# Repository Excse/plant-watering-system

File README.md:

# 🌱 Smart Plant Pot

An ESP32-based plant pot project combining soil moisture sensing, Home Assistant integration, a custom PCB, and a planned automatic watering system with an internal reservoir.

[Getting started](#getting-started) · [Firmware guide](firmware/README.md) · [Hardware guide](docs/README.md) · [Development checklist](#development-checklist) · [PCB previews](#pcb-previews)

> **Work in progress:** firmware and electronics are being prototyped. Soil moisture readings and MQTT discovery are implemented; the complete automatic watering pot is still under development.

## Current status

| Area | Available today | Still planned |
| --- | --- | --- |
| Firmware | GPIO 34 moisture readings, calibration, Wi-Fi, MQTT state and Home Assistant discovery | Pump control, reservoir sensing, automatic watering and manual watering commands |
| Electronics | Editable KiCad schematic, board layout and generated previews | Prototype assembly and validation |
| Pot | Integrated reservoir and electronics concept | Printable design, assembly instructions and plant trials |

The repository currently supports testing moisture sensing on an ESP32 development
board. Pot CAD files and a complete assembly guide are not included yet.

## The plant pot

The pot is intended to take care of routine watering while keeping everything in one unit:

- A soil moisture sensor measures when the plant needs water.
- A pump delivers water from an internal reservoir.
- A water level sensor monitors the reservoir so the system knows when it needs refilling.
- Custom firmware manages sensing, watering, and communication with Home Assistant over Wi-Fi and MQTT.
- A custom PCB and printable pot bring the electronics and water system together, with access for refilling and maintenance.

Home Assistant will provide moisture and reservoir readings, watering status, and manual watering controls. Automatic watering should run on the pot itself; its behavior during network outages is part of the firmware design.

## Getting started

To try the current firmware, you need an ESP32 development board compatible with
PlatformIO's `esp32dev` target, an analog soil moisture sensor, PlatformIO, Wi-Fi,
and an MQTT broker. Home Assistant is optional for initial testing. The
[firmware guide](firmware/README.md) lists the requirements and setup instructions.

Clone the repository with its library submodule. The commands below use GitHub SSH access, including for the `rhadar` submodule:

```sh
git clone --recurse-submodules git@github.com:Excse/plant-watering-system.git
cd plant-watering-system/firmware
```

For an existing checkout, run `git submodule update --init --recursive` from the repository root.

Follow the [firmware guide](firmware/README.md) to wire the sensor, configure Wi-Fi and MQTT, flash the ESP32, calibrate readings, and connect Home Assistant.

## Development checklist

Start by testing the sensors and pump together, then use that prototype to finish the PCB and pot design. Validate automatic watering under supervision before an extended plant trial.

### Sensors and pump

- [ ] Validate moisture calibration and reading stability in the intended soil.
- [ ] Choose and test a water level sensor for the reservoir.
- [ ] Control the pump manually and measure water delivered for different runtimes.
- [ ] Test the power supply with the ESP32, sensors, and pump running together.

### Firmware and Home Assistant

- [ ] Add reservoir level, watering status, and manual pump control to MQTT discovery.
- [ ] Implement configurable moisture thresholds and watering amounts, with time for water to soak in between cycles.
- [ ] Stop or prevent watering on invalid readings or an empty reservoir, and enforce a maximum pump runtime.
- [ ] Define and test behavior after power loss and during Wi-Fi or MQTT outages.

### Custom PCB

- [ ] Complete the schematic using the tested components and power requirements.
- [ ] Finish PCB layout and resolve relevant ERC/DRC findings.
- [ ] Manufacture and assemble a prototype board, then test sensing, pump control, and Wi-Fi together.

### Integrated pot

- [ ] Plan the soil area, reservoir capacity, and space for the pump, sensors, and PCB.
- [ ] Design water routing and an electronics compartment protected from moisture.
- [ ] Add access for refilling, cleaning, and repairs, then print and test the pot for fit and leaks.

### Complete system

- [ ] Test watering amounts and sensor behavior with everything installed in the pot.
- [ ] Run an extended plant trial and refine calibration and watering settings.
- [ ] Document the parts, assembly, firmware setup, and maintenance.

## Schematic

*Click the preview to open the full-size SVG.*

Open [pcb/pcb.kicad_pro](pcb/pcb.kicad_pro) in KiCad 10 to explore the editable design. GitHub Actions keeps the preview updated when the schematic or project files change on the default branch.

Local symbols, footprints, and 3D models are organized in [pcb/libraries/](pcb/libraries/README.md).

## PCB previews

<p align="center">
  
</p>

*3D view of the current design. Click to enlarge; components appear where a 3D model is assigned.*

<table>
  <tr><th>Front</th><th>Back</th></tr>
  <tr>
    <td></td>
    <td></td>
  </tr>
</table>

*Copper and silkscreen, cropped to the board. Click either preview to enlarge; the back is mirrored to show the underside.*

The [KiCad checks and previews workflow](https://github.com/Excse/plant-watering-system/actions/workflows/kicad.yml) runs **ERC** and **DRC** for hardware changes and updates these previews on the default branch. See [hardware documentation](docs/README.md) for report and preview-generation details.

## Repository layout

| Directory | Contents |
| --- | --- |
| [firmware/](firmware/) | ESP32 source, PlatformIO configuration, and setup instructions |
| [pcb/](pcb/) | KiCad project, schematic, PCB, and local component libraries |
| [docs/](docs/) | Schematic and PCB previews, plus hardware automation documentation |
| [scripts/](scripts/) | KiCad rule checks and preview generation |
| [.github/workflows/](.github/workflows/) | Automation for hardware checks and preview updates |

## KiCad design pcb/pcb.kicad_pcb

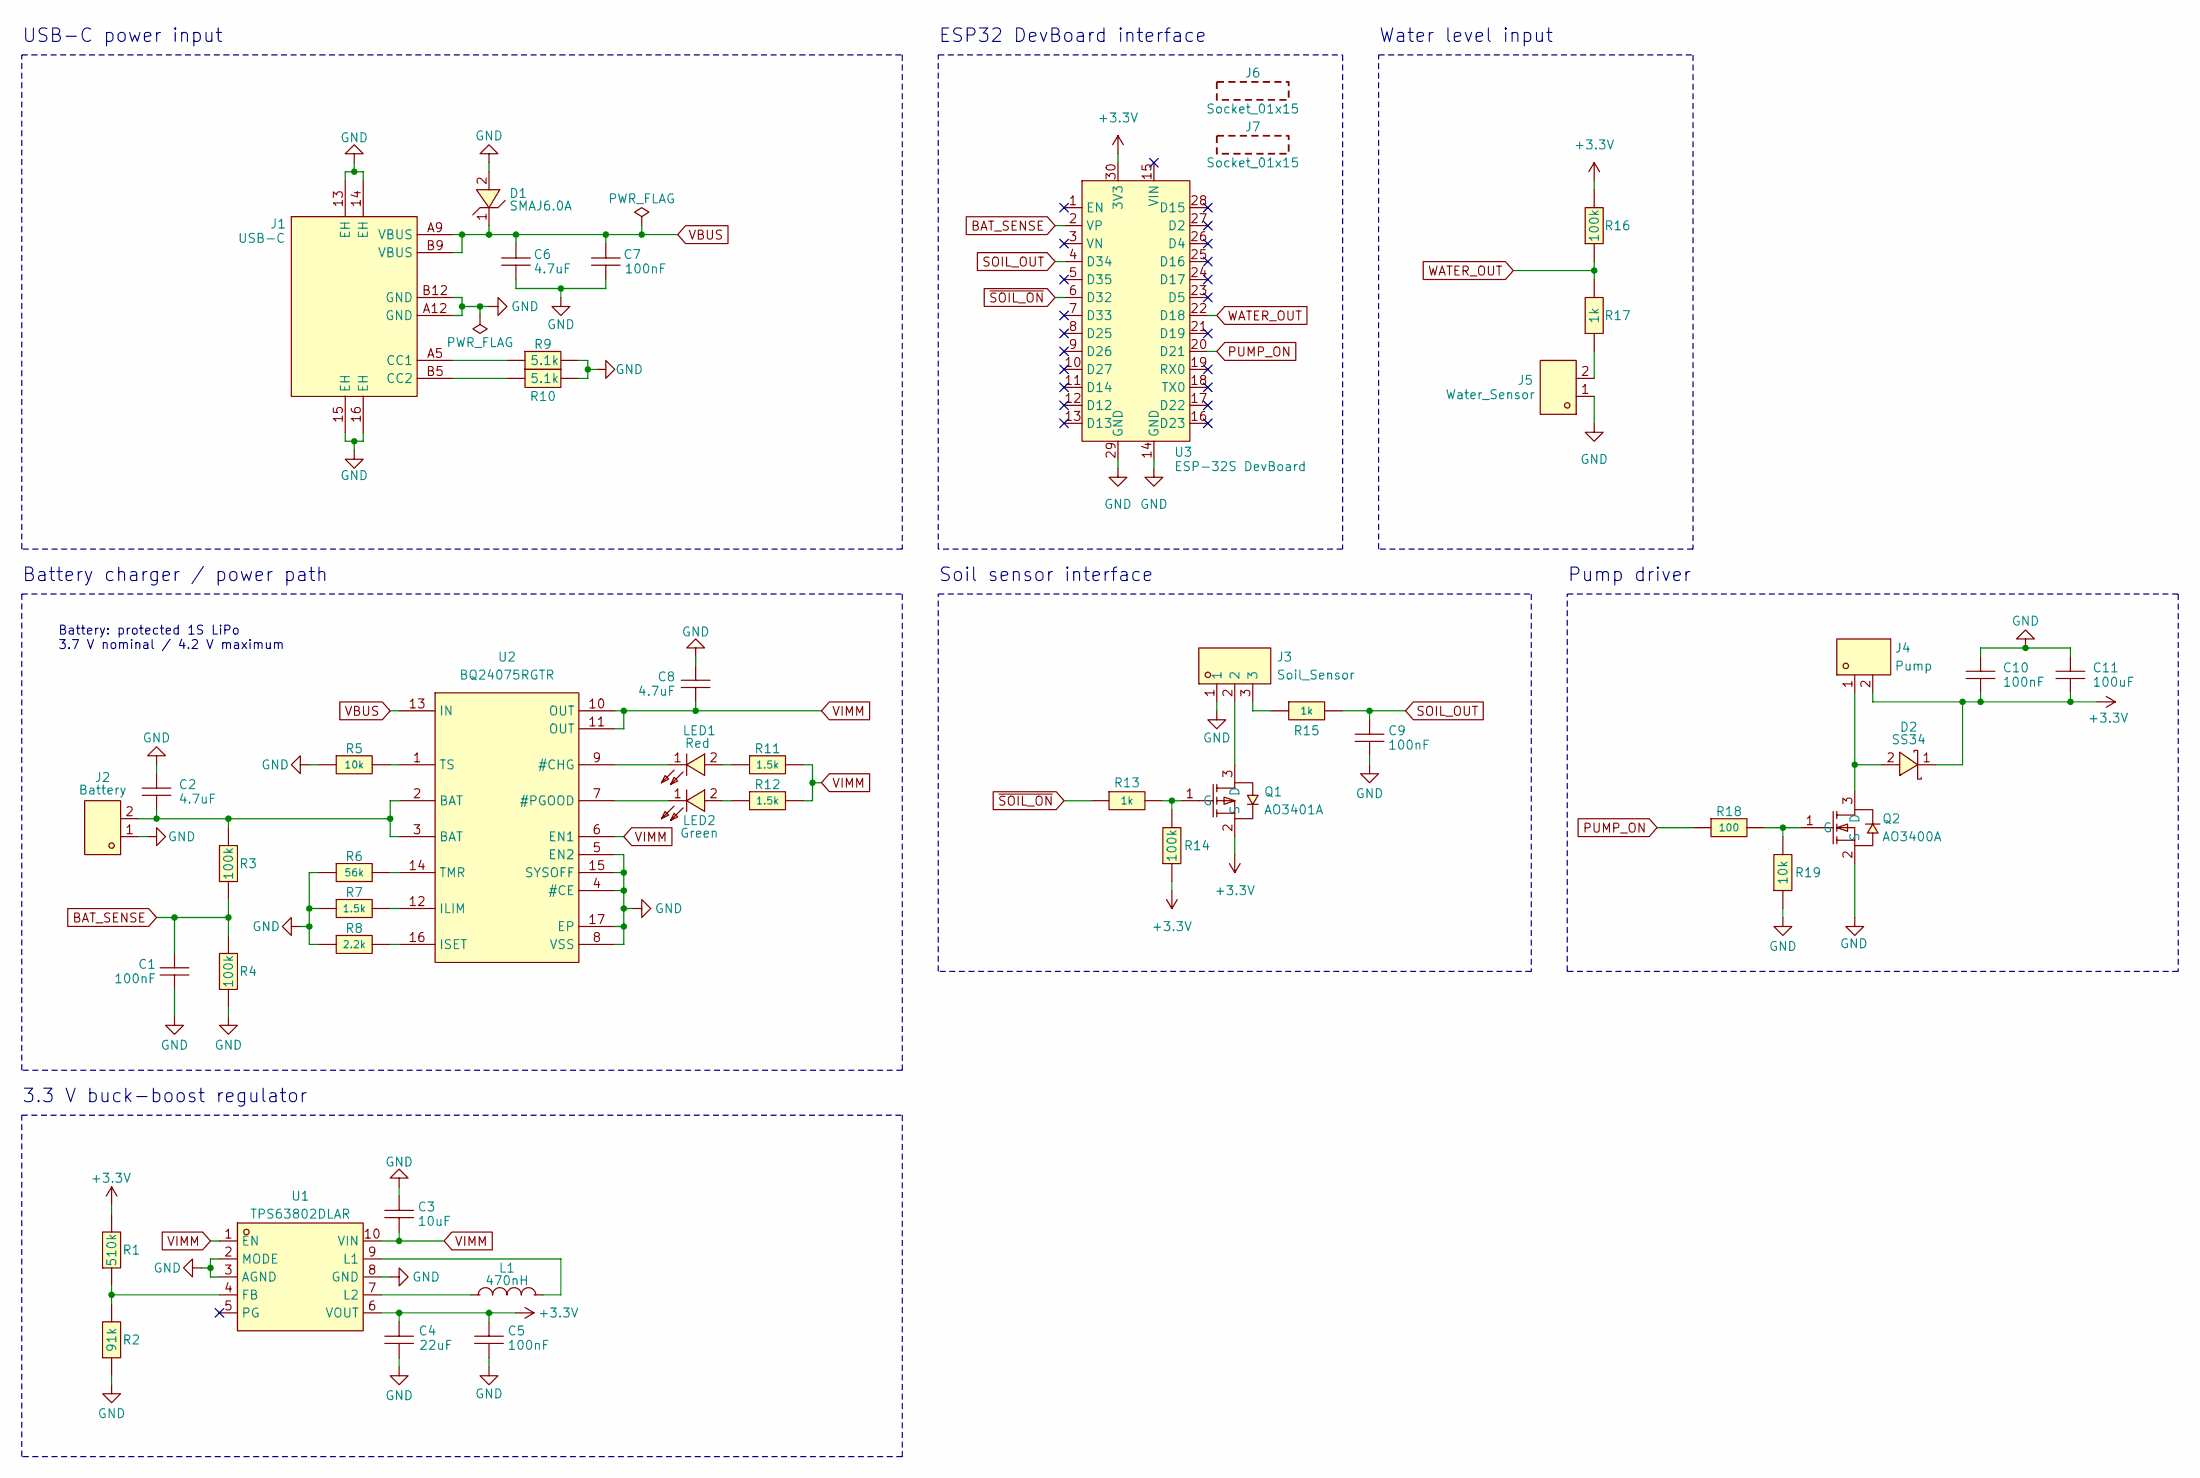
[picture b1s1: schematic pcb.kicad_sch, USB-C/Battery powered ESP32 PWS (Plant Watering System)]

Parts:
C1, C5, C7, C9, C10: 100nF; C_0402_1005Metric; Voltage 16V; MPN CL05B104KO5NNNC; LCSC Part C1525
C2, C6, C8: 4.7uF; C_0603_1608Metric; Voltage 16V; MPN CL10A475KO8NNNC; LCSC Part C19666
C3: 10uF; C_0603_1608Metric; Voltage 25V; MPN CL10A106MA8NRNC; LCSC Part C96446
C4: 22uF; C_0603_1608Metric; Voltage 6.3V; MPN CL10A226MQ8NRNC; LCSC Part C59461
C11: 100uF; C_0805_2012Metric; Voltage 6.3V; MPN GRM21BR60J107ME15L; LCSC Part C141660
D1: SMAJ6.0A; D_SMA; MPN SMAJ6.0A; LCSC Part C223993
D2: SS34; D_SMA; MPN SS34; LCSC Part C8678
J1: USB-C; USB_C_Receptacle_HX_TYPE-C-6P; MPN HX TYPE-C 6PIN; LCSC Part C18357552
J2: Battery; JST_PH_S2B-PH-SM4-TB_1x02-1MP_P2.00mm_Horizontal; MPN S2B-PH-SM4-TB(LF)(SN); LCSC Part C295747
J3: Soil_Sensor; JST_PH_S3B-PH-SM4-TB_1x03-1MP_P2.00mm_Horizontal; MPN S3B-PH-SM4-TB(LF)(SN); LCSC Part C265101
J4: Pump; JST_PH_S2B-PH-SM4-TB_1x02-1MP_P2.00mm_Horizontal; MPN S2B-PH-SM4-TB(LF)(SN); LCSC Part C295747
J5: Water_Sensor; JST_PH_S2B-PH-SM4-TB_1x02-1MP_P2.00mm_Horizontal; MPN S2B-PH-SM4-TB(LF)(SN); LCSC Part C295747
J6, J7: Socket_01x15; MPN 2541FV-15P-B; LCSC Part C25503121
L1: 470nH; L_Murata_DFE201610P; MPN DFE201612E-R47M=P2; LCSC Part C668312
LED1: Red; LED_0805_2012Metric; MPN NCD0805R1; LCSC Part C84256
LED2: Green; LED_0805_2012Metric; MPN KT-0805G; LCSC Part C2297
Q1: AO3401A; SOT-23-3; MPN AO3401A; LCSC Part C15127
Q2: AO3400A; SOT-23-3; MPN AO3400A; LCSC Part C20917
R1: 510k; R_0402_1005Metric; MPN 0402WGF5103TCE; LCSC Part C11616
R2: 91k; R_0603_1608Metric; MPN 0603WAF9102T5E; LCSC Part C23265
R3, R4, R14, R16: 100k; R_0402_1005Metric; MPN 0402WGF1003TCE; LCSC Part C25741
R5, R19: 10k; R_0402_1005Metric; MPN 0402WGF1002TCE; LCSC Part C25744
R6: 56k; R_0402_1005Metric; MPN 0402WGF5602TCE; LCSC Part C25796
R7, R11, R12: 1.5k; R_0402_1005Metric; MPN 0402WGF1501TCE; LCSC Part C25867
R8: 2.2k; R_0402_1005Metric; MPN 0402WGF2201TCE; LCSC Part C25879
R9, R10: 5.1k; R_0402_1005Metric; MPN 0402WGF5101TCE; LCSC Part C25905
R13, R15, R17: 1k; R_0402_1005Metric; MPN 0402WGF1001TCE; LCSC Part C11702
R18: 100; R_0402_1005Metric; MPN 0402WGF1000TCE; LCSC Part C25076
U1: TPS63802DLAR; Texas_VSON-HR-10_2x3mm_P0.5mm; MPN TPS63802DLAR; LCSC Part C2845237
U2: BQ24075RGTR; QFN-16-1EP_3x3mm_P0.5mm_EP1.7x1.7mm; MPN BQ24075RGTR; LCSC Part C15464
U3: ESP-32S DevBoard; ESP-32S_USB-C_CH340_DevBoard

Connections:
+3.3V: C4.2, C5.1, C10.1, C11.1, D2.1, J4.2, Q1.2 (S), R1.2, R14.1, R16.2, U1.6 (VOUT), U3.30 (3V3)
BAT_SENSE: C1.2, R3.1, R4.2, U3.2 (VP)
GND: C1.1, C2.2, C3.2, C4.1, C5.2, C6.1, C7.1, C8.2, C9.1, C10.2, C11.2, D1.2, J1.13 (EH), J1.14 (EH), J1.15 (EH), J1.16 (EH), J1.A12 (GND), J1.B12 (GND), J2.1, J3.1, J5.1, Q2.2 (S), R2.1, R4.1, R5.1, R6.1, R7.1, R8.1, R9.2, R10.2, R19.1, U1.2 (MODE), U1.3 (AGND), U1.8 (GND), U2.4 (#CE), U2.5 (EN2), U2.8 (VSS), U2.15 (SYSOFF), U2.17 (EP), U3.14 (GND), U3.29 (GND)
unnamed: C2.1, J2.2, R3.2, U2.2 (BAT), U2.3 (BAT)
unnamed: J1.A5 (CC1), R9.1
unnamed: J1.B5 (CC2), R10.1
unnamed: J3.3, R15.1
unnamed: J5.2, R17.1
unnamed: LED1.2, R11.1
unnamed: LED2.2, R12.1
unnamed: J3.2, Q1.3 (D)
unnamed: Q1.1 (G), R13.2, R14.2
unnamed: D2.2, J4.1, Q2.3 (D)
unnamed: Q2.1 (G), R18.2, R19.2
unnamed: R1.1, R2.2, U1.4 (FB)
unnamed: L1.2, U1.9 (L1)
unnamed: L1.1, U1.7 (L2)
unnamed: LED1.1, U2.9 (#CHG)
unnamed: LED2.1, U2.7 (#PGOOD)
unnamed: R7.2, U2.12 (ILIM)
unnamed: R8.2, U2.16 (ISET)
unnamed: R6.2, U2.14 (TMR)
unnamed: R5.2, U2.1 (TS)
PUMP_ON: R18.1, U3.20 (D21)
SOIL_OUT: C9.2, R15.2, U3.4 (D34)
VBUS: C6.2, C7.2, D1.1, J1.A9 (VBUS), J1.B9 (VBUS), U2.13 (IN)
VIMM: C3.1, C8.1, R11.2, R12.2, U1.1 (EN), U1.10 (VIN), U2.6 (EN1), U2.10 (OUT), U2.11 (OUT)
WATER_OUT: R16.1, R17.2, U3.22 (D18)
~SOIL_ON: R13.1, U3.6 (D32)

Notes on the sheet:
USB-C power input
Water level input
Battery: protected 1S LiPo 3.7 V nominal / 4.2 V maximum
Soil sensor interface
ESP32 DevBoard interface
3.3 V buck-boost regulator
Pump driver
Battery charger / power path

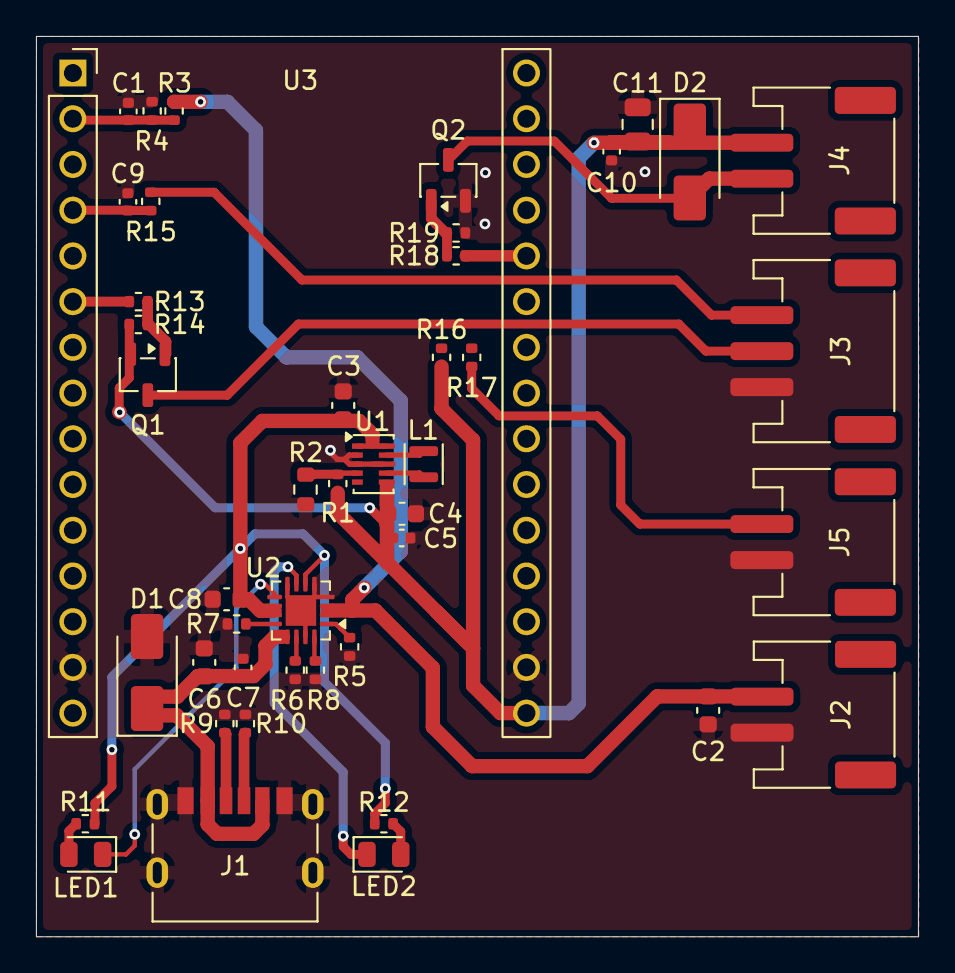
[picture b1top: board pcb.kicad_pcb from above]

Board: 2 copper layers, 49.0 x 50.0 mm, 45 parts (0 on the bottom side), 29 nets.
